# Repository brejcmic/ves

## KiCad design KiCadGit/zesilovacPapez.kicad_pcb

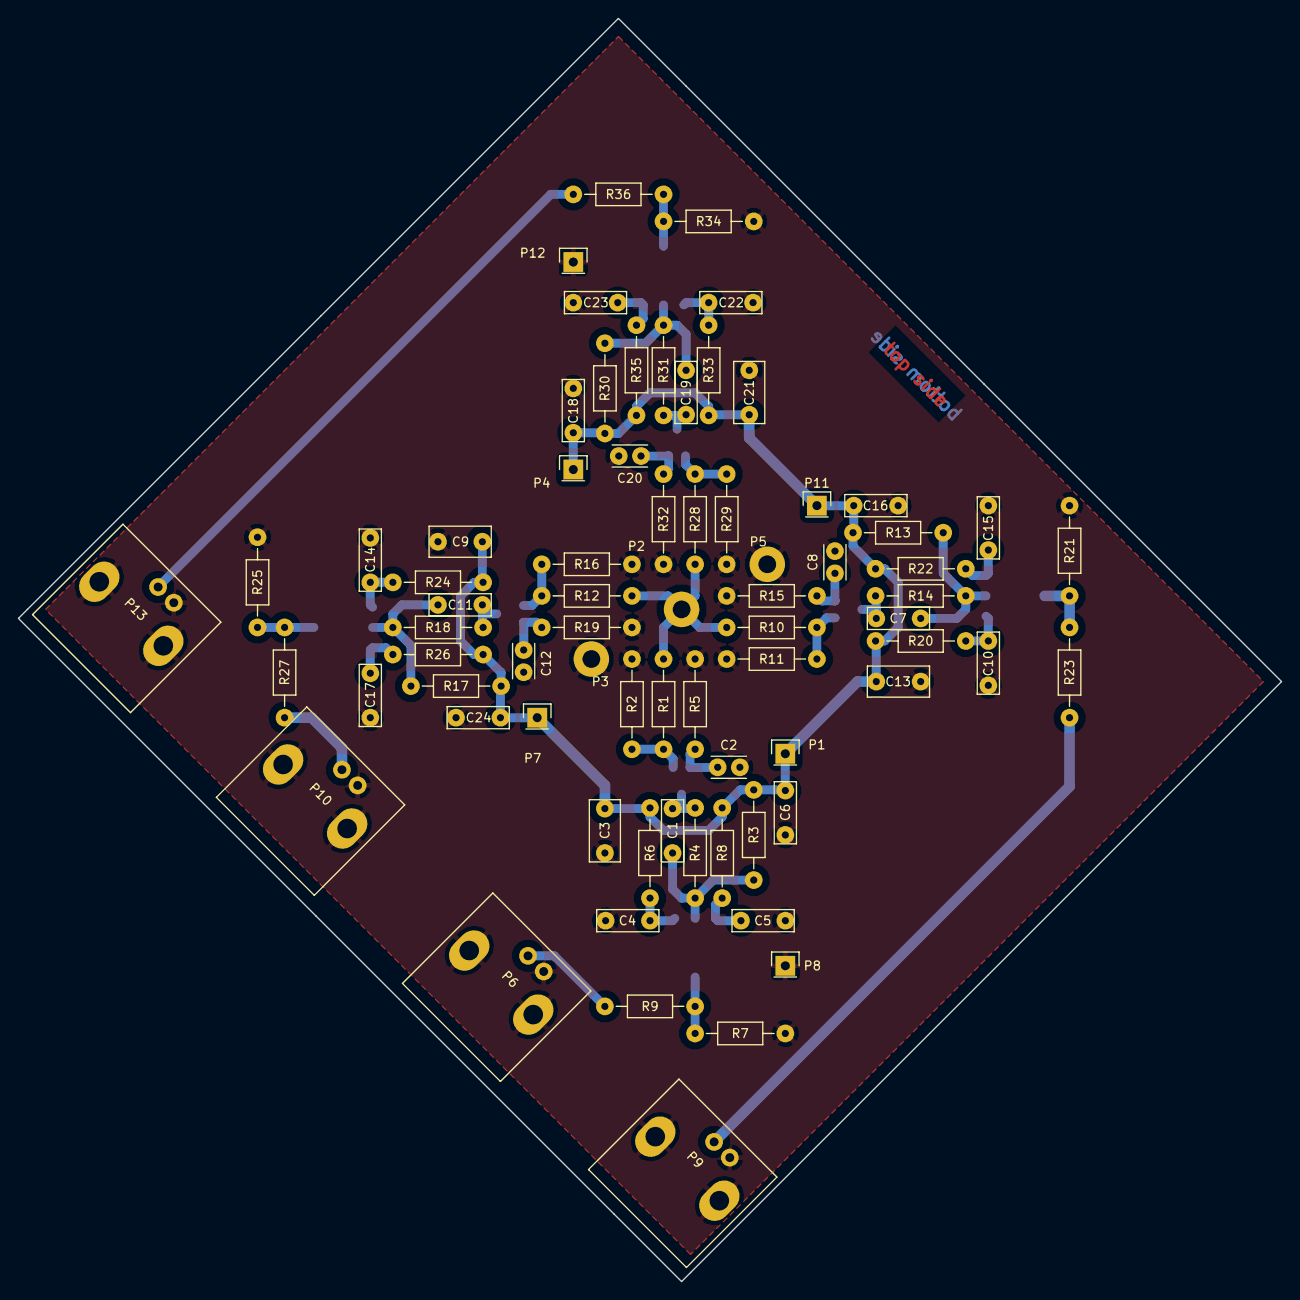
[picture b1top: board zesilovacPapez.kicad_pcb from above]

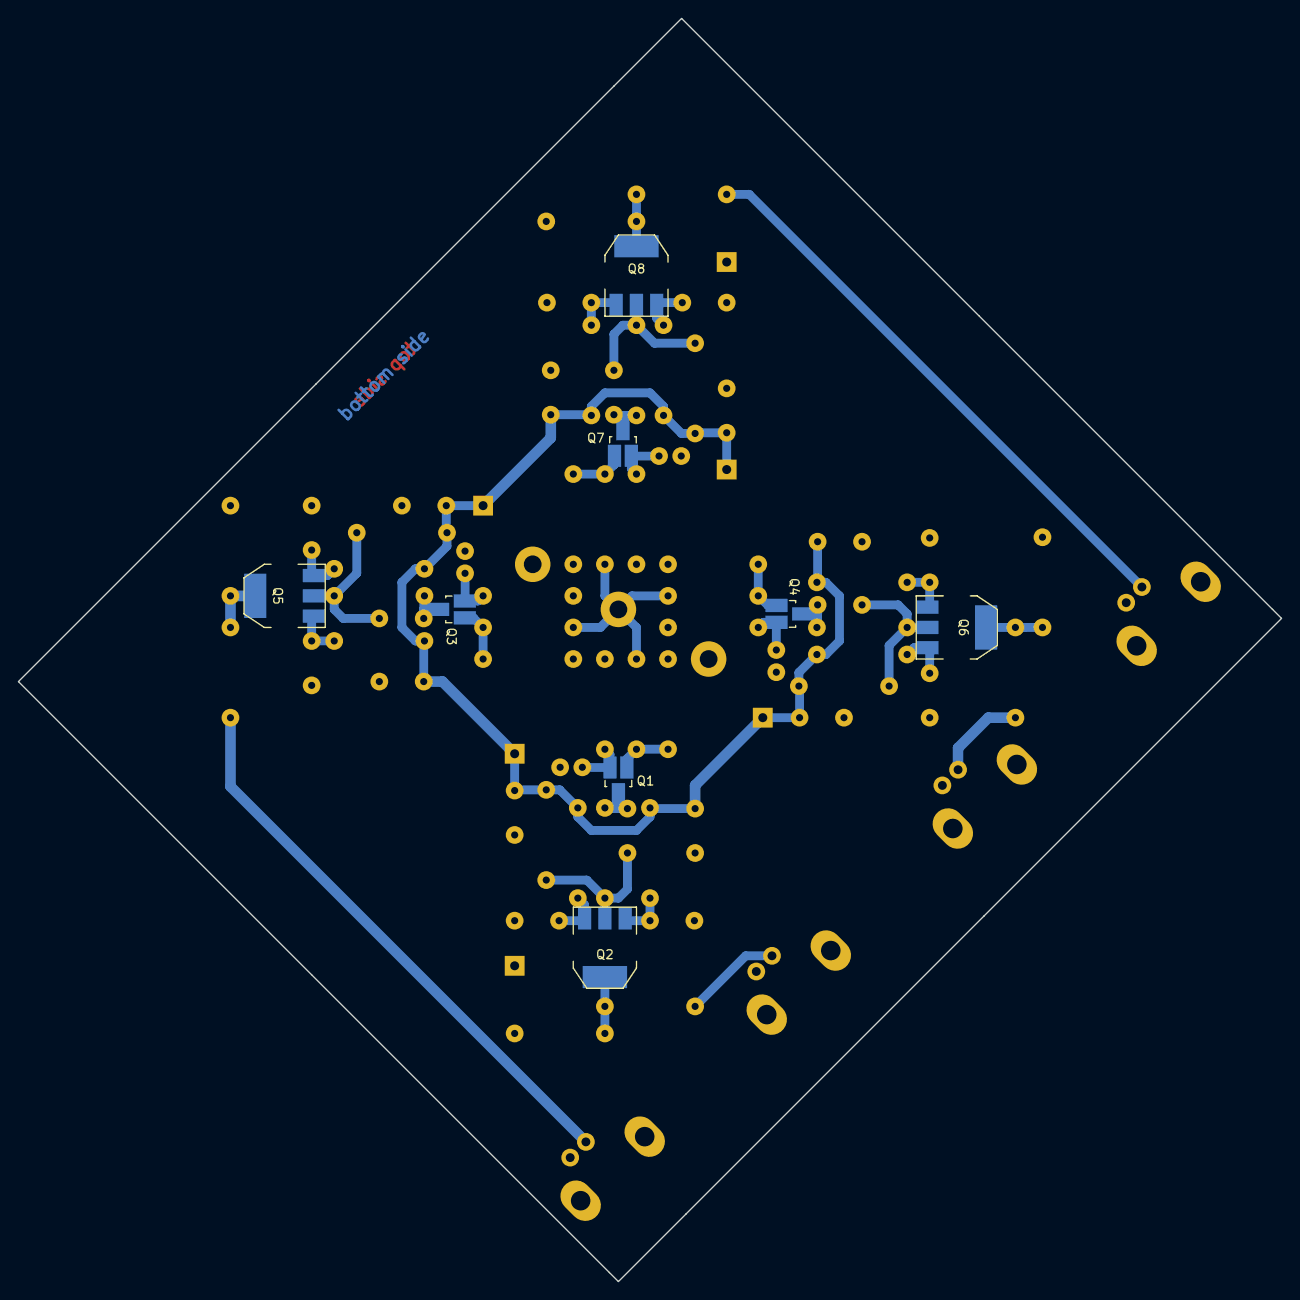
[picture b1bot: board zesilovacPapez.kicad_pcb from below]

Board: 2 copper layers, 142.2 x 142.2 mm, 81 parts (8 on the bottom side), 35 nets.

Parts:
C1, C7, C11, C19: 220p; C_Rect_L7_W2.5_P5
C2, C8, C12, C20: 220p; C_Rect_L4_W2.5_P2.5
C3, C9, C13, C21: 1M; C_Rect_L7_W3.5_P5
C4, C10, C14, C22: 1k2; C_Rect_L7_W2.5_P5
C5, C15, C17, C23: 1k; C_Rect_L7_W2.5_P5
C6, C16, C18, C24: 100p; C_Rect_L7_W2.5_P5
P1, P4, P7, P11: VDD; Pin_Header_Straight_1x01
P2: INPUT; Pin_Header_Straight_1x01
P3, P5, P8, P12: GND; Pin_Header_Straight_1x01
P6, P9, P10, P13: BNC; BNC_Socket_TYCO-AMP
Q1, Q3, Q4, Q7: BFR92; SOT-23_Handsoldering
Q2, Q5, Q6, Q8: BFG31; SOT-223
R1, R7, R10, R12, R21, R25, R28, R34: 120R; Resistor_Horizontal_RM10mm
R2, R11, R16, R29: 220R; Resistor_Horizontal_RM10mm
R3, R13, R17, R30: 154R; Resistor_Horizontal_RM10mm
R4, R14, R18, R31: 100R; Resistor_Horizontal_RM10mm
R5, R15, R19, R32: 47R; Resistor_Horizontal_RM10mm
R6, R8, R20, R22, R24, R26, R33, R35: 12R; Resistor_Horizontal_RM10mm
R9, R23, R27, R36: 10R; Resistor_Horizontal_RM10mm

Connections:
GND: C2.2, C3.1, C4.2, C5.1, C6.1, C8.2, C9.1, C10.2, C12.2, C13.1, C14.2, C15.1, C16.1, C17.1, C18.1, C20.2, C21.1, C22.2, C23.1, C24.1, P3.1, P5.1, P6.2, P8.1, P9.2, P10.2, P12.1, P13.2, R2.2, R5.2, R7.2, R11.2, R15.2, R16.2, R19.2, R21.2, R25.2, R29.2, R32.2, R34.2
unnamed: C1.1, Q2.2, R3.2, R4.1
unnamed: C1.2, Q1.3, R4.2
unnamed: C2.1, Q1.2, R5.1
unnamed: C4.1, Q2.1, R6.2
unnamed: C5.2, Q2.3, R8.2
unnamed: C7.1, Q5.2, R13.2, R14.1
unnamed: C7.2, Q3.3, R14.2
unnamed: C8.1, Q3.2, R15.1
unnamed: C10.1, Q5.1, R20.2
unnamed: C11.1, Q6.2, R17.2, R18.1
unnamed: C11.2, Q4.3, R18.2
unnamed: C12.1, Q4.2, R19.1
unnamed: C14.1, Q6.1, R24.2
unnamed: C15.2, Q5.3, R22.2
unnamed: C17.2, Q6.3, R26.2
unnamed: C19.1, Q8.2, R30.2, R31.1
unnamed: C19.2, Q7.3, R31.2
unnamed: C20.1, Q7.2, R32.1
unnamed: C22.1, Q8.1, R33.2
unnamed: C23.2, Q8.3, R35.2
unnamed: P2.1, R1.2, R10.2, R12.2, R28.2
unnamed: P6.1, R9.1
unnamed: P9.1, R23.1
unnamed: P10.1, R27.1
unnamed: P13.1, R36.1
unnamed: Q1.1, R1.1, R2.1
unnamed: Q2.4, R7.1, R9.2
unnamed: Q3.1, R10.1, R11.1
unnamed: Q4.1, R12.1, R16.1
unnamed: Q5.4, R21.1, R23.2
unnamed: Q6.4, R25.1, R27.2
unnamed: Q7.1, R28.1, R29.1
unnamed: Q8.4, R34.1, R36.2
VCC: C3.2, C6.2, C9.2, C13.2, C16.2, C18.2, C21.2, C24.2, P1.1, P4.1, P7.1, P11.1, R3.1, R6.1, R8.1, R13.1, R17.1, R20.1, R22.1, R24.1, R26.1, R30.1, R33.1, R35.1

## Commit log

2015-10-02 prvni commit
2015-10-02 Hotove navody na nelinearni rezistory, feroelektricke kondenzatory a vysokofrekvencni civky.
2015-10-02 Hotovy navod na pajeni a mereni rc nad 1MHz.
2015-10-04 Doplneny podklady pro zbyvajici navody. Zadny neni hotovy.
2015-10-09 Navody byly rozdeleny do vice stranek.
2015-10-12 Doplneny obrazky k jednotlivym uloham.
2015-10-14 První tři úlohy jsou plně popsány, pájení se popisovat víc nebude. Je třeba dodělat polovodiče a fotovoltaické panely.
2015-10-15 Hotovy navod na cvika rc do 1 MHz.
2015-10-16 Hotovy navod pro mereni RC nad 1 MHz
2015-10-19 Hotovy navod na polovodice
2015-10-19 Hotove nelinearni rezistory
2015-10-19 Hotove vf civky
2015-10-19 Vsechny navody vystaveny na moodle. Chybi fotovoltaicke panely.
2015-10-20 Hotove vsechny navody, predano na moodle.
2015-11-06 Opraveny chyby v zadani navodu - predevsim polovodice Nakresleni popisku pro pripravky měreni tranzistoru a zesilovac
2015-11-13 popisky k pripravkum
2016-01-21 Vf zesilovac pro Papeze v KiCad
2016-01-21 v gitignore doplneny soubory pro KiCad
2016-01-21 Opraveny chyby v navodu a vyplnovaci listek pro testy v Edubasi
2016-01-26 Finalni verze RF zesilovace pred vyrobou. Upraveny dleky privodu, popisy a velikosti plosek.
2016-02-02 DPS zesilovac: -upraveny diry na 0,8 mm pro kohouta a zvetseny centrealni a zemnici otvory pro privod kabelu.
2016-02-18 Zesilova-Papez: - vytvoreny podklady pro osazovani
2016-02-24 Zesilovac Papez: - uprava potisku BNC pro vyrobu v Cine nebo Pragoboardu - vygenerovani gerber dat
2016-10-03 Uprava poradi uloh a zakladni schema pripravku pro mereni diod a tranzistoru.
2016-10-04 Dotvorene schema mereni tranzistoru - nutno predelat pripojne body meraku a zdroju na svorkovnice ARK
2016-10-04 Predelany svorkovnice
2016-10-05 Navrzena DPS pro mereni tranzistoru. Vyroba musi byt v Pragoboardu.
2016-10-19 Tranzistory predany k vyrobe
2016-11-02 Uprava zadani el. obvodu a polovodicu.
2016-11-02 DPS Tranzistory: - opraveny chyby v desce, nyni by mela byt pouzitelna az do 30 V UCE
2016-11-15 DPS Tranzisotry: - snizeno zesileni zpetne vazby - pridan odpor ke kondenzatoru sample-hold tak, aby vytvoril integracni clanek.
2016-11-24 Nova verze piskace pro pajeni
2016-12-01 Nova verze DPS pro pajeni
2016-12-01 Uprava navodu - nove vzorky a pajeni
2016-12-01 Uprava vyplnovaciho listku pro pololetni test
2017-06-13 PapezVybijec: -schema a zakladni rozmisteni soucastek
2017-06-13 PapezVybijec: - hotova dps
2017-06-13 PapezVybijec: - nahledy dps pro prvni kontrolu
2017-06-14 testy: - vyplnovaci listky
2017-06-14 gitignore: - pridany knihovny
2017-06-14 PapezVybijec: - pridany knihovny
2017-06-14 PapezVybijec: - opraveny rozmery nytu
2017-06-14 PapezVybijec: - hotove podklady, - pridany navrhove pravidla
2017-09-20 Eagle: - vybijec pro Papeze - tranzistory pred odeslanim do pragoboardu - navrh zdroju proudu
2017-09-22 Priprava pro semestr 2017-2018
2017-09-22 Novy popisek pro pripravek
2017-09-25 Tranzistory: Pravidla
2017-09-25 Tranzistory: pridana objednavka
2017-09-25 Doplneny chybejici soubory GERBER
2017-09-26 Tranzistory: - opravena dalsi chybka v napojeni emitoru a serioveho rezistoru
2017-10-10 PrednaskyEN: 1. prednaska, cast nazvoslovi, cast zakladni soucastky hotovo
2017-10-11 PrednaskaEN: hotovo pr1 - hotova prednaska na prvni hodinu
2017-10-26 Pridany anglicke prednasky - hotove P1-P3 x rozpracovana P4
2017-10-30 Oprava navodu cvik pro mereni nad 1MHz a pristroj Agilent E4991A
2017-10-31 Temer hotova anglicka prednaska 4 o kondenzatorech
2017-11-01 Hotova prednaska P4 o kondenzatorech
2017-11-02 Opravy v prednaskach a navodech na cviceni
2017-11-03 Priprava na prednasku 5
2017-11-09 Hotova prednaska P5 pro anglicany
2017-11-10 Oprava chyb v prednasce P5
2017-11-12 Rozpracovana verze prednasky P6 pro anglicany.
2017-11-13 U prednasky P6 upraven obr1 a pridelan prvni ukol mereni.
2017-11-14 Pridan slajd k P6
2017-11-15 Pridany testy Hajek
2017-11-15 Cast prednasky pro anglicany P6
2017-11-20 Prednaska P6 pro anglicany
2017-11-20 Projekt pro Papeze - bocnik k baterkam
2017-11-21 Hotovy vykonovy obvod simulujici zenerovu doidu
2017-11-21 Odstraneny nepotrebne soubory
2017-11-21 Zacatek prace na prednasce P7 pro anglicany
2017-11-21 Prednaska P7 pro anglicany ujasneny charakteristiky
2017-11-22 Hotovy panel pro Papezovu zenerku - zmensene prumery padu
2017-11-22 Hotova prednaska P7 pro anglicany
2017-11-23 Opraveny chyby v prednasce P7 pro anglicany
2017-11-28 Priprava na prednasku P8 pro anglicany
2017-11-28 Prednaska P8 pro anglicany - fotoodpory
2017-11-28 Prednaska P8 pro anglicany, pridana spousta obrazku
2017-11-29 Hotova prednaska P8 pro anglicany
2017-12-05 Priprava na prednasku P9 anglicani
2017-12-05 Pridany obrazky do prednasky P9 pro anglicany
2017-12-05 Pridelany dalsi obrazky do prednasky P9 pro anglicany.
2017-12-06 Hotova prednaska P9 pro anglicany
2017-12-13 Priprava prezentace P10 pro anglicany
2017-12-18 Hotova prednaska P10 pro anglicany.
2018-01-02 Pridany prednasky od Jirky Hajka
2018-01-02 Priprava prednasek P11 pro anglicany
2018-01-03 oprava prednasky P10 pro anglicany - stupne F na stupne C
2018-01-03 Hotova prednaska P11 pro anglicany
